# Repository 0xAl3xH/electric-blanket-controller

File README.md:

# Electric Blanket Controller 

## About The Project

An excellent way to stay warm while camping/overlanding on a tight electrical energy budget is with a 12V electric blanket. With a blanket such as [this one](https://www.amazon.com/gp/product/B01N21MI0Z) under a sleeping bag, you can stay fairly warm. However, these blankets don't typically come with temperature control and you can easily overheat a couple hours after power on. In addition to it being uncomfortable, there's power being wasted here to achieve a comfortable temperature. The electric blanket controller uses a MOSFET as a switch to apply a duty cycle to the power coming into the blanket, giving users a choice between different levels of heat. 

## Goals

- [ ] Efficient - as most users are using 12V electric blankets off grid, it's important that the controller doesn't dissipate much power
- [ ] Easy to use - no modifications to the blankets or car power port, plug and play
- [ ] Replicable - so more overlanders can stop overheating with these blankets and save energy

## Milestones

- [ x ] Find appropriate hardware for controller
- [ x ] Test hardware and find duty cycle
- [ x ] Create PCB 
- [ x ] Write firmware
- [ x ] Test firmware
- [ x ] Build controller on real PCB with v1.0.0 firmware
- [ x ] Design a 3D printed case

## Getting Started

Flash the `.ino` file using your favorite ATTiny programmer. I didn't have one handy so ended up using an [Arduino Uno](https://www.instructables.com/How-to-Program-an-Attiny85-From-an-Arduino-Uno) to flash the ATTiny. The ATTiny needs to run at 1 MHz clock for this project, which should be the default from factory. The `hardware` directory contains the circuit board schematic and board files in `pcb` as well as a 3D printed case with tight and loose tolerances to account for the variablility in 3D printers. 

## License

Distributed under the MIT License. See LICENSE.txt for more information.

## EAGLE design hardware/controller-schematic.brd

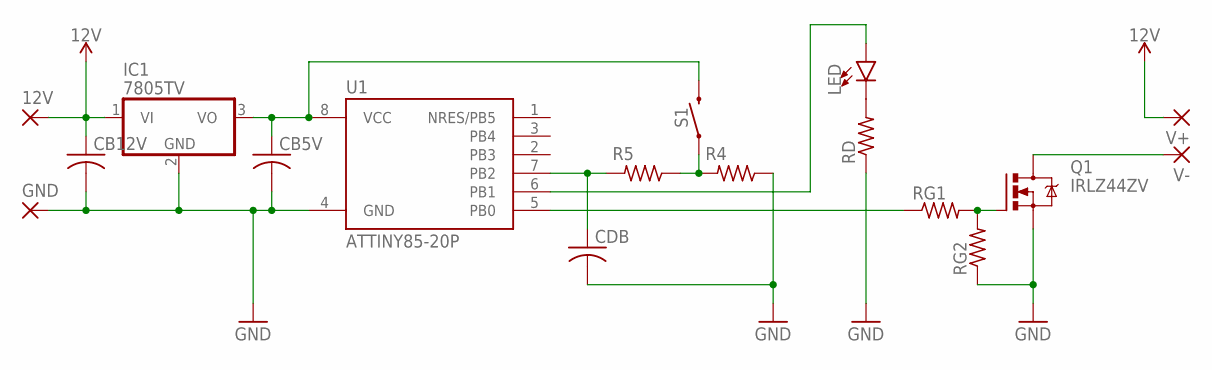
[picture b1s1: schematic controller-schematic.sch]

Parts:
12V: SMD5; SMD2,54-5,08
CB5V, CB12V: C-US050-030X075; C050-030X075
CDB: C-US050-030X075; C050-030X075
GND: SMD5; SMD2,54-5,08
IC1: 7805TV; TO220V
LED: LED3MM; LED_3MM
Q1: IRLZ44ZV; TO220BV
R4, R5: R-US_0207/7; 0207/7
RD: R-US_0207/7; 0207/7
RG1, RG2: R-US_0207/7; 0207/7
S1: MOMENTARY-SWITCH-SPST-PTH-6.0MM; TACTILE_SWITCH_PTH_6.0MM
U1: ATTINY85-20P; PDIP08_300MIL
V+: SMD5; SMD2,54-5,08
V-: SMD5; SMD2,54-5,08

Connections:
5V: CB5V.1, IC1.3 (VO), S1.3 (2), U1.8 (VCC)
12V: 12V.1, CB12V.1, IC1.1 (VI), V+.1
GND: CB5V.2, CB12V.2, CDB.2, GND.1, IC1.2 (GND), Q1.S, R4.1, RD.1, RG2.1, U1.4 (GND)
unnamed: RG1.1, U1.5 (PB0)
unnamed: Q1.G, RG1.2, RG2.2
unnamed: Q1.D, V-.1
unnamed: LED.K (C), RD.2
unnamed: LED.A, U1.6 (PB1)
unnamed: R4.2, R5.1, S1.1
unnamed: CDB.1, R5.2, U1.7 (PB2)

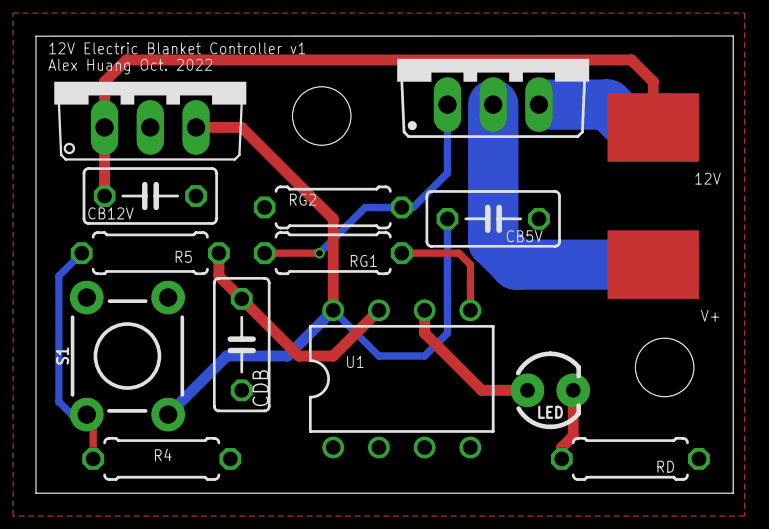
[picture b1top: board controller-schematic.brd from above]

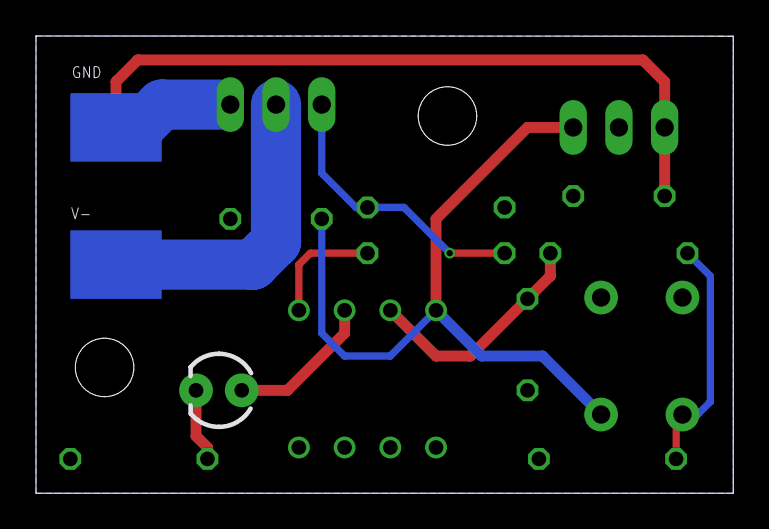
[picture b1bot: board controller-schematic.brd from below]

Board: 2 copper layers, 38.7 x 25.4 mm, 17 parts (2 on the bottom side), 10 nets.

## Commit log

2022-11-01 Add ATTiny85 firmware for electric blanket controller
2022-11-01 Design controller schematic and complete PCB layout
2022-11-01 Add Eagle project files gitignore
2022-11-01 Fix LED not turning off in flash function
2022-11-01 Update goals
2022-11-21 Adjust LED flash timing for better UX
2022-11-21 Fix interupt bug
2022-11-21 Finish v1.0 firmware
    TODO: figure out why debounce doesn't work very well next time have
    access to oscilloscope
2022-11-21 Add passives values to schematic and board
2022-11-21 Add configuration file for VS Code
2022-11-21 Fix level being inverted bug and formatting
2022-11-21 Fix code formatting
2023-05-14 Ignore vscode configs
2023-05-14 Use state machine for button debouncing logic
2023-05-14 Update readme milestone
2023-05-14 Add EAGLE gitignore files
2023-05-14 Make / move files to PCB directory
2023-05-14 Add 3D printed case files
2023-05-14 Add hardware documentation

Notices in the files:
parts and their libraries:
SparkFun-LED: Licensing: Creative Commons ShareAlike 4.0 International - https://creativecommons.org/licenses/by-sa/4.0
